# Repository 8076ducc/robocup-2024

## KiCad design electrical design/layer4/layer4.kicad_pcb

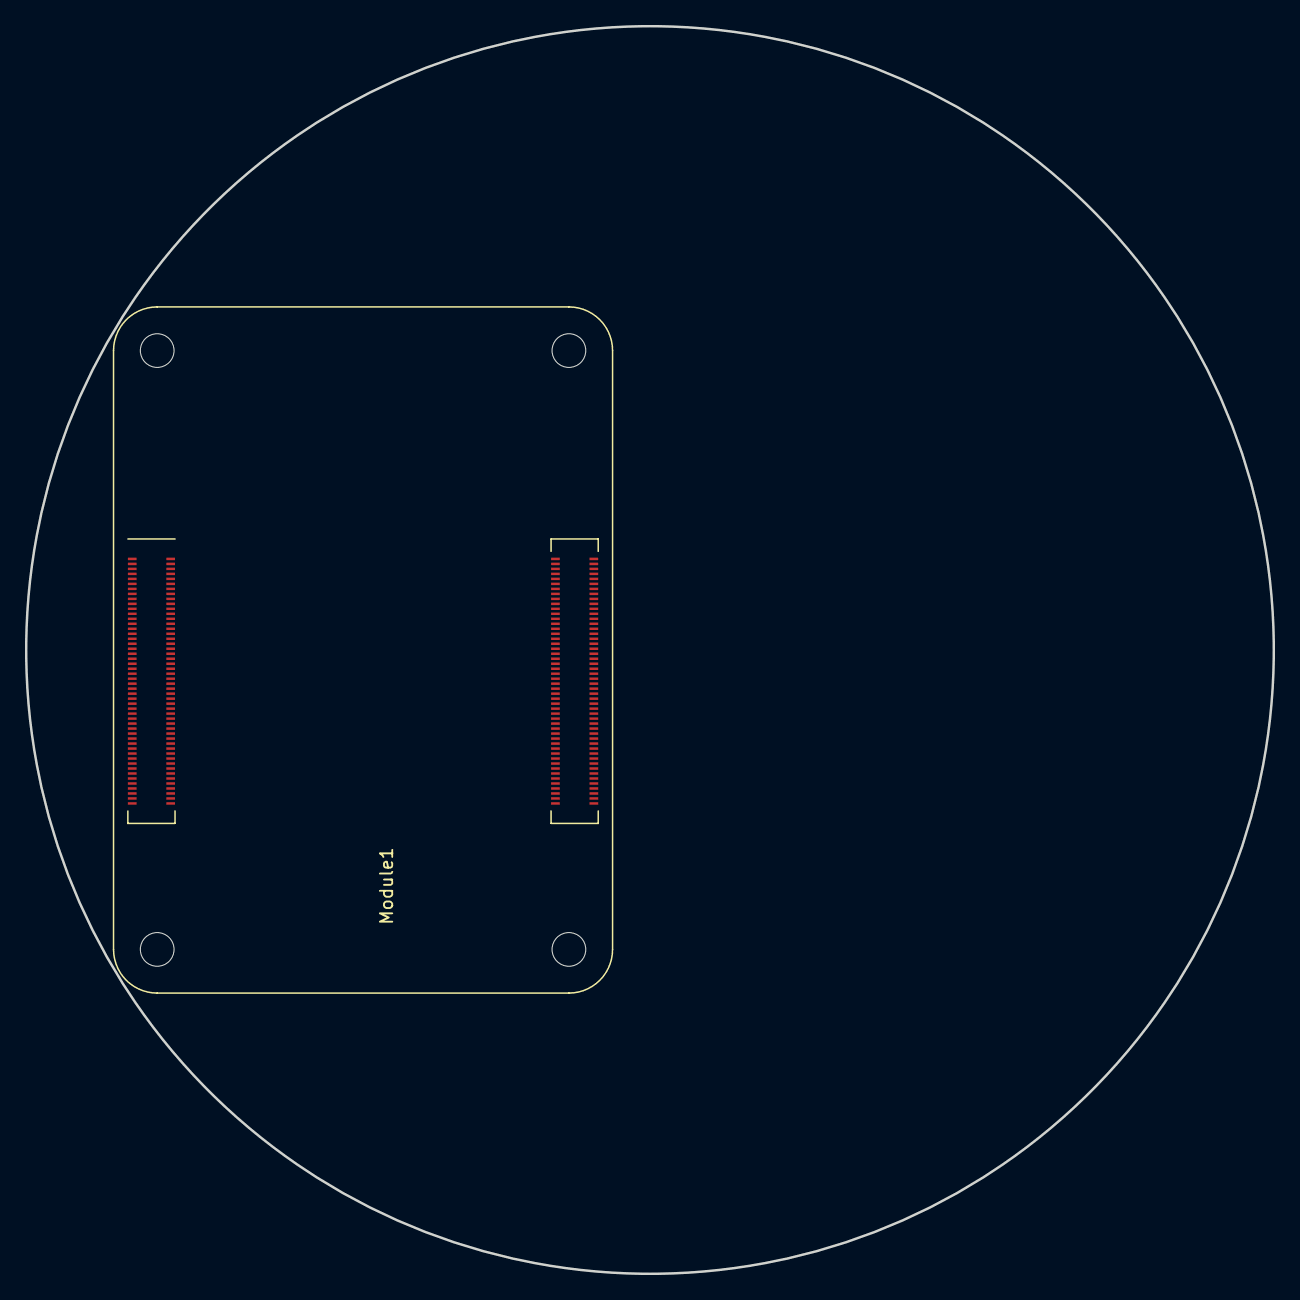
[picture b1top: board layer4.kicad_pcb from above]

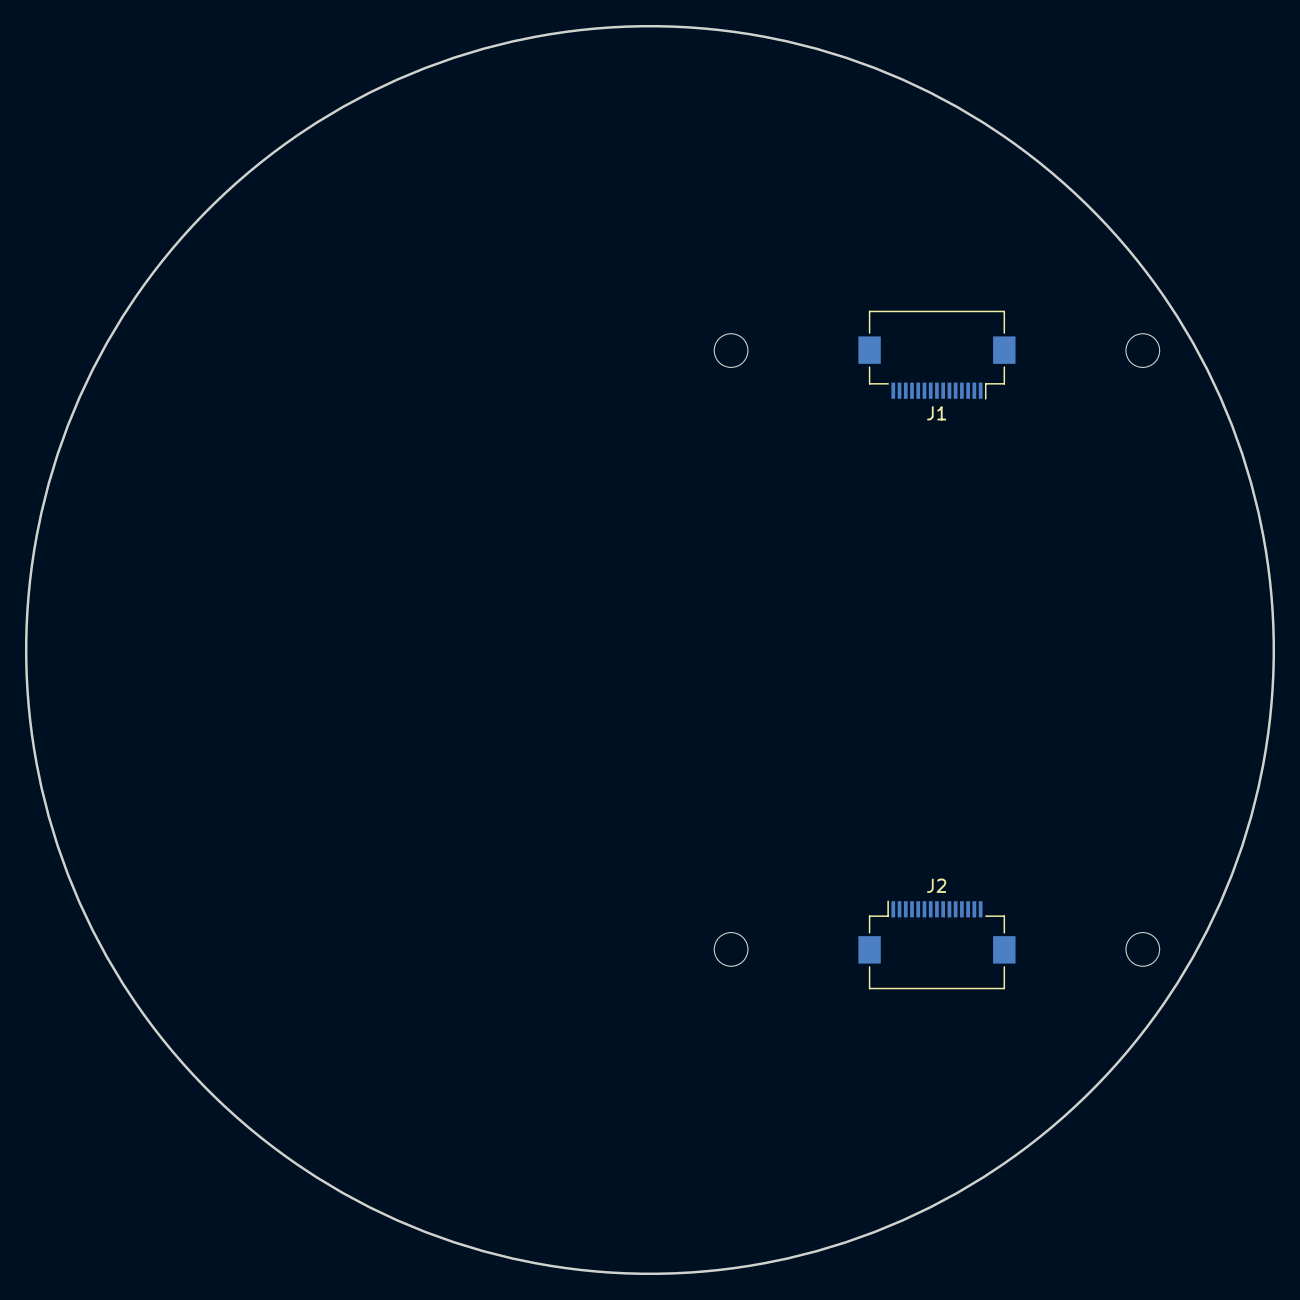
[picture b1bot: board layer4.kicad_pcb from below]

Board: 2 copper layers, 100.0 x 100.0 mm, 3 parts (2 on the bottom side), 20 nets, no tracks yet.

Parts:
J1, J2: Conn_01x15_Female; Hirose_FH12-15S-0.5SH_1x15-1MP_P0.50mm_Horizontal
Module1: ComputeModule4-CM4; Raspberry-Pi-4-Compute-Module

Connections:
+3V3: J1.15, J2.15, Module1.78 (GPIO_VREF(1.8v/3.3v_Input)), Module1.84 (+3.3v_(Output)), Module1.86 (+3.3v_(Output))
+5V: Module1.77 (+5v_(Input)), Module1.79 (+5v_(Input)), Module1.81 (+5v_(Input)), Module1.83 (+5v_(Input)), Module1.85 (+5v_(Input)), Module1.87 (+5v_(Input))
/rpi1/CAM0_C_N: J1.8, Module1.140 (CAM0_C_N)
/rpi1/CAM0_C_P: J1.9, Module1.142 (CAM0_C_P)
/rpi1/CAM0_D0_N: J1.2, Module1.128 (CAM0_D0_N)
/rpi1/CAM0_D0_P: J1.3, Module1.130 (CAM0_D0_P)
/rpi1/CAM0_D1_N: J1.5, Module1.134 (CAM0_D1_N)
/rpi1/CAM0_D1_P: J1.6, Module1.136 (CAM0_D1_P)
/rpi1/CAM1_C_N: J2.8, Module1.127 (CAM1_C_N)
/rpi1/CAM1_C_P: J2.9, Module1.129 (CAM1_C_P)
/rpi1/CAM1_D0_N: J2.2, Module1.115 (CAM1_D0_N)
/rpi1/CAM1_D0_P: J2.3, Module1.117 (CAM1_D0_P)
/rpi1/CAM1_D1_N: J2.5, Module1.121 (CAM1_D1_N)
/rpi1/CAM1_D1_P: J2.6, Module1.123 (CAM1_D1_P)
/rpi1/CAM_GPIO: J1.11, J2.11, Module1.97 (Camera_GPIO)
/rpi1/ID_SCL: J2.13, Module1.35 (ID_SC)
/rpi1/ID_SDA: J2.14, Module1.36 (ID_SD)
/rpi1/SCL0: J1.13, Module1.80 (SCL0)
/rpi1/SDA0: J1.14, Module1.82 (SDA0)
GND: J1.1, J1.4, J1.7, J1.10, J2.1, J2.4, J2.7, J2.10, Module1.1 (GND), Module1.2 (GND), Module1.7 (GND), Module1.8 (GND), Module1.13 (GND), Module1.14 (GND), Module1.22 (GND), Module1.23 (GND), Module1.32 (GND), Module1.33 (GND), Module1.42 (GND), Module1.43 (GND), Module1.52 (GND), Module1.53 (GND), Module1.59 (GND), Module1.60 (GND), Module1.65 (GND), Module1.66 (GND), Module1.71 (GND), Module1.74 (GND), Module1.98 (GND), Module1.107 (GND), Module1.108 (GND), Module1.113 (GND), Module1.114 (GND), Module1.119 (GND), Module1.120 (GND), Module1.125 (GND), Module1.126 (GND), Module1.131 (GND), Module1.132 (GND), Module1.137 (GND), Module1.138 (GND), Module1.144 (GND), Module1.150 (GND), Module1.155 (GND), Module1.156 (GND), Module1.161 (GND), Module1.162 (GND), Module1.167 (GND), Module1.168 (GND), Module1.173 (GND), Module1.174 (GND), Module1.179 (GND), Module1.180 (GND), Module1.185 (GND), Module1.186 (GND), Module1.191 (GND), Module1.192 (GND), Module1.197 (GND), Module1.198 (GND)

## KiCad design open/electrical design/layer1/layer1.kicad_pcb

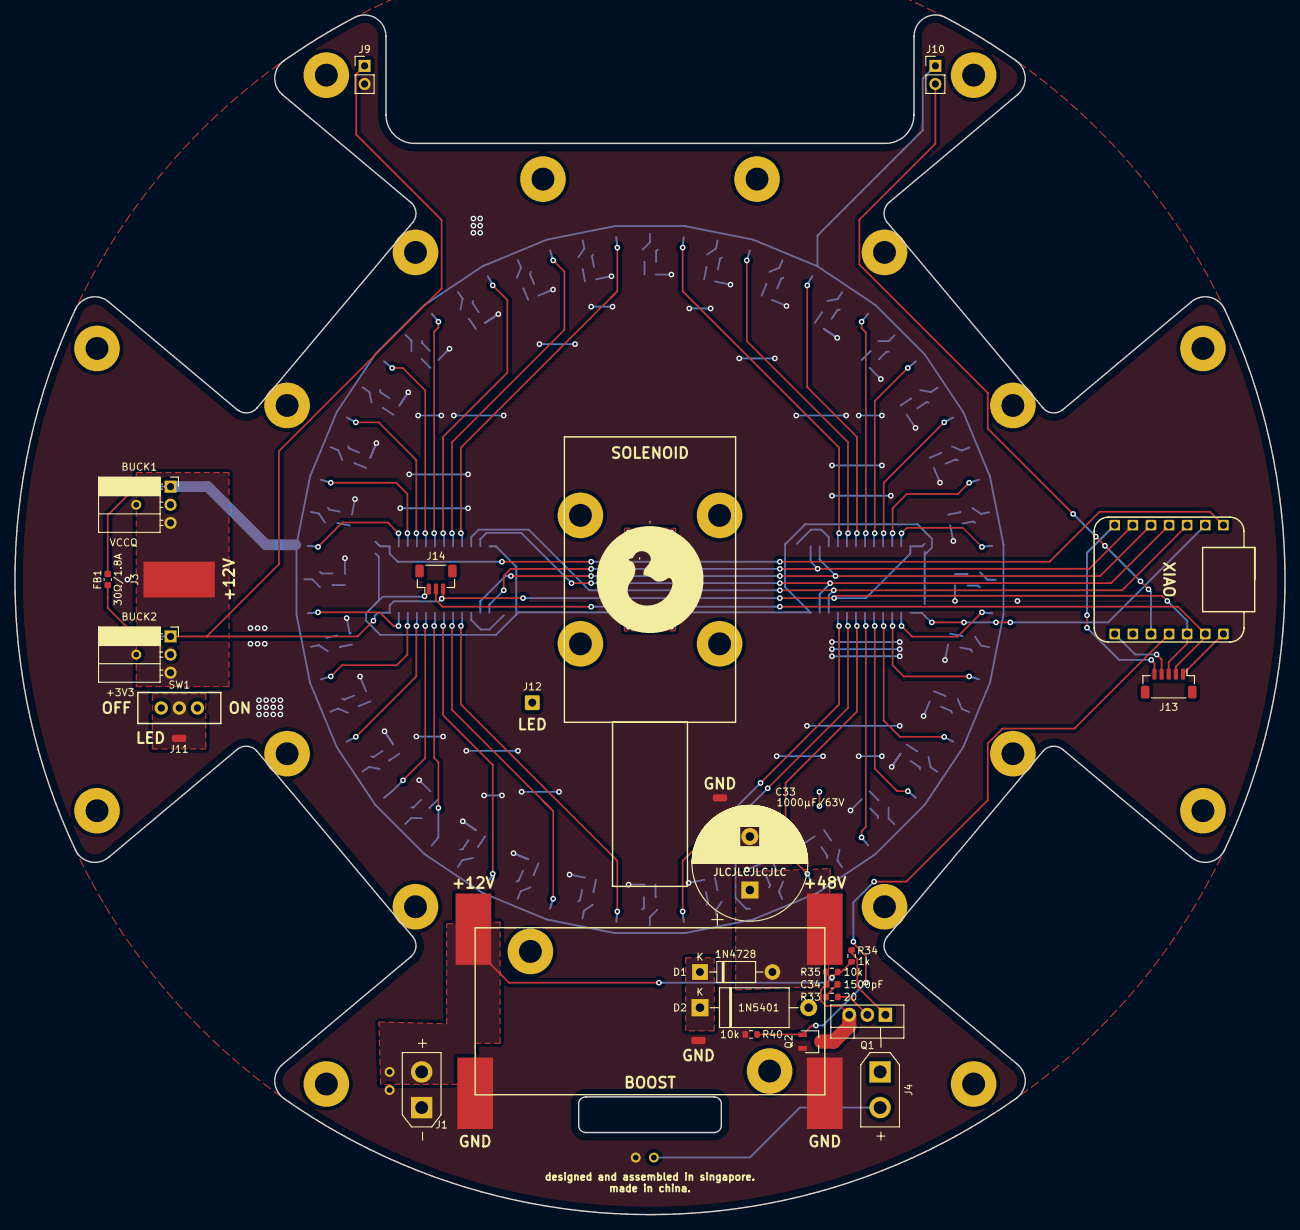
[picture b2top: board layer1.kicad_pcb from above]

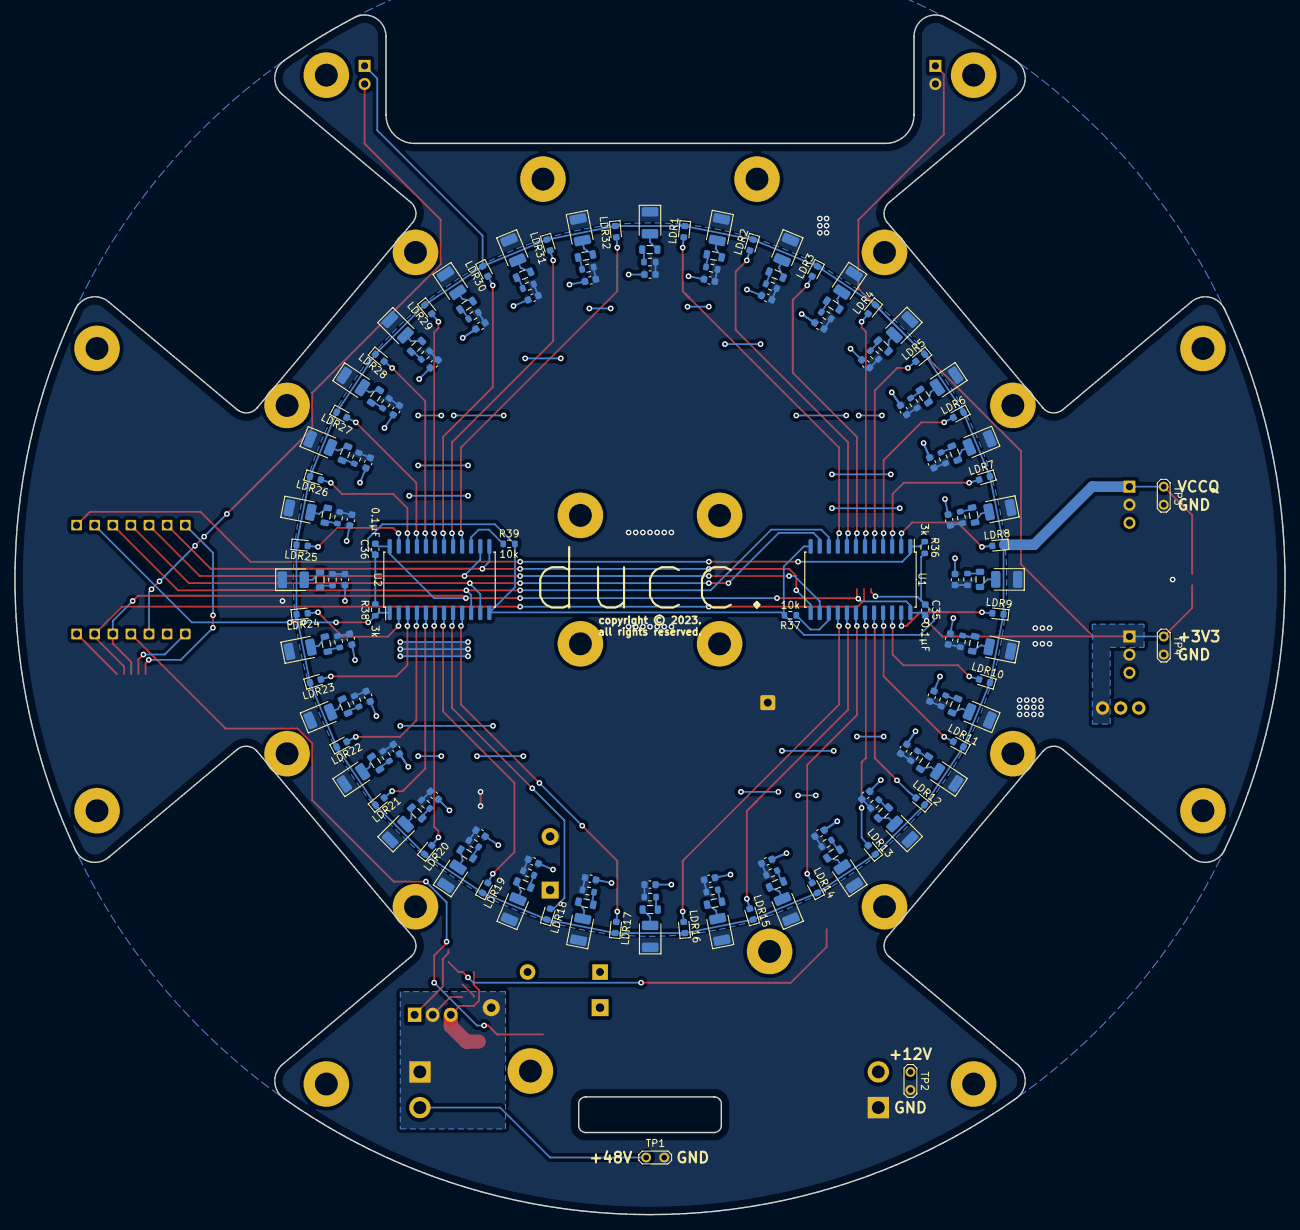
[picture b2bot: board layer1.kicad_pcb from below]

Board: 2 copper layers, 178.0 x 168.1 mm, 226 parts (172 on the bottom side), 122 nets.

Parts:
BUCK1: VCCQ; PinSocket_1x03_P2.54mm_Horizontal
BUCK2: +3V3; PinSocket_1x03_P2.54mm_Horizontal
C1, C2, C3, C4, C5, C6, C7, C8, C9, C10, C11, C12, C13, C14, C15, C16, C17, C18, C19, C20, C21, C22, C23, C24, C25, C26, C27, C28, C29, C30, C31, C32: 1uF; C_0603_1608Metric
C33: 1000µF/63V; CP_Radial_D16.0mm_P7.50mm
C34: 1500pF; C_0603_1608Metric
C35, C36: 0.1μF; C_0603_1608Metric
D1: 1N4728; D_DO-41_SOD81_P10.16mm_Horizontal
D2: 1N5401; D_DO-27_P15.24mm_Horizontal
FB1: 30Ω/1.8A; C_0603_1608Metric
H1, H2, H3, H4, H5, H6, H7, H8, H9, H10, H11, H12, H13, H14, H15, H16, H17, H18, H19, H20, H21, H22, H23, H24: MountingHole; MountingHole_3.2mm_M3_Pad
J1: XT30-F; AMASS_XT30UPB-F_1x02_P5.0mm_Vertical
J2, J11, J15: Conn_01x01_Socket; SolderWirePad_1x01_SMD_1x2mm
J3, J5, J6, J7, J8: Conn_01x01_Socket; SolderWirePad_1x01_SMD_5x10mm
J4: XT30PW-F; AMASS_XT30UPB-F_1x02_P5.0mm_Vertical
J9, J10: Conn_01x02_Pin; PinHeader_1x02_P2.54mm_Vertical
J12: Conn_01x01_Socket; SolderWire-0.5sqmm_1x01_D0.9mm_OD2.1mm
J13: SH1.0 5P; JST_SH_BM05B-SRSS-TB_1x05-1MP_P1.00mm_Vertical
J14: SH1.0 3P; JST_SH_BM03B-SRSS-TB_1x03-1MP_P1.00mm_Vertical
L1, L2, L3, L4, L5, L6, L7, L8, L9, L10, L11, L12, L13, L14, L15, L16, L17, L18, L19, L20, L21, L22, L23, L24, L25, L26, L27, L28, L29, L30, L31, L32: 10µH; L_0805_2012Metric
LDR1, LDR2, LDR3, LDR4, LDR5, LDR6, LDR7, LDR8, LDR9, LDR10, LDR11, LDR12, LDR13, LDR14, LDR15, LDR16, LDR17, LDR18, LDR19, LDR20, LDR21, LDR22, LDR23, LDR24, LDR25, LDR26, LDR27, LDR28, LDR29, LDR30, LDR31, LDR32: ALS-PT19-315C; D_0603_1608Metric
LED1, LED2, LED3, LED4, LED5, LED6, LED7, LED8, LED9, LED10, LED11, LED12, LED13, LED14, LED15, LED16, LED17, LED18, LED19, LED20, LED21, LED22, LED23, LED24, LED25, LED26, LED27, LED28, LED29, LED30, LED31, LED32: WHITE 3528; CP_EIA-3528-12_Kemet-T
Q1: MOSFET-NCH-FQP30N06L; TO-220-3_Vertical
Q2: MOSFET-NCH-AO3404A; TSOT-23
R1, R2, R3, R4, R5, R6, R7, R8, R9, R10, R11, R12, R13, R14, R15, R16, R17, R18, R19, R20, R21, R22, R23, R24, R25, R26, R27, R28, R29, R30, R31, R32: 0R39; R_0603_1608Metric
R33: 20; R_0603_1608Metric
R34: 1k; R_0603_1608Metric
R35, R37, R39, R40: 10k; R_0603_1608Metric
R36, R38: 3k; R_0603_1608Metric
SW1: SW_SPDT; SWITCH_SPDT_PTH_11.6X4.0MM
TP1, TP2, TP3, TP4: TestPoint_2Pole; TestPoint_2Pads_Pitch2.54mm_Drill0.8mm
U1, U2: CD74HC4067SM; SOIC-24W_7.5x15.4mm_P1.27mm
U3: MOUDLE-SEEEDUINO-XIAO-ESP32C3; xiao-esp32c3

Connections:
+3V3: BUCK2.1, C35.1, C36.1, FB1.1, J9.1, J13.3, J14.3, SW1.1 (A), TP4.1, U1.24 (VCC), U2.24 (VCC), U3.12 (3V3)
+5V: J13.1, U3.14 (5V)
+12V: BUCK1.3, BUCK2.3, J1.2, J3.1, J5.1, R34.1, R35.1, TP2.1
+48V: C33.1, D1.2 (A), J4.2, J7.1, TP1.1
/BALL: J10.2, U3.10 (PA5_A9_D9_MISO)
/LED: C1.1, C2.1, C3.1, C4.1, C5.1, C6.1, C7.1, C8.1, C9.1, C10.1, C11.1, C12.1, C13.1, C14.1, C15.1, C16.1, C17.1, C18.1, C19.1, C20.1, C21.1, C22.1, C23.1, C24.1, C25.1, C26.1, C27.1, C28.1, C29.1, C30.1, C31.1, C32.1, J11.1, J12.1, R1.1, R2.1, R3.1, R4.1, R5.1, R6.1, R7.1, R8.1, R9.1, R10.1, R11.1, R12.1, R13.1, R14.1, R15.1, R16.1, R17.1, R18.1, R19.1, R20.1, R21.1, R22.1, R23.1, R24.1, R25.1, R26.1, R27.1, R28.1, R29.1, R30.1, R31.1, R32.1, SW1.2 (B)
/MUX1OUT: R36.1, U1.1 (COM), U3.1 (PA02_A0_D0)
/MUX2OUT: R38.1, U2.1 (COM), U3.2 (PA4_A1_D1)
/RX: J13.4, U3.8 (PB09_A7_D7_RX)
/S0: U1.10 (S0), U2.10 (S0), U3.3 (PA10_A2_D2)
/S1: U1.11 (S1), U2.11 (S1), U3.4 (PA11_A3_D3)
/S2: U1.14 (S2), U2.14 (S2), U3.5 (PA8_A4_D4_SDA)
/S3: U1.13 (S3), U2.13 (S3), U3.6 (PA9_A5_D5_SCL)
/SOLENOIDON: Q2.1 (G), R40.1, U3.11 (PA6_A10_D10_MOSI)
/TX: J13.5, U3.7 (PB08_A6_D6_TX)
GND: BUCK1.2, BUCK2.2, C1.2, C2.2, C3.2, C4.2, C5.2, C6.2, C7.2, C8.2, C9.2, C10.2, C11.2, C12.2, C13.2, C14.2, C15.2, C16.2, C17.2, C18.2, C19.2, C20.2, C21.2, C22.2, C23.2, C24.2, C25.2, C26.2, C27.2, C28.2, C29.2, C30.2, C31.2, C32.2, C33.2, J1.1, J2.1, J6.1, J8.1, J9.2, J15.1, LED1.1 (K), LED2.1 (K), LED3.1 (K), LED4.1 (K), LED5.1 (K), LED6.1 (K), LED7.1 (K), LED8.1 (K), LED9.1 (K), LED10.1 (K), LED11.1 (K), LED12.1 (K), LED13.1 (K), LED14.1 (K), LED15.1 (K), LED16.1 (K), LED17.1 (K), LED18.1 (K), LED19.1 (K), LED20.1 (K), LED21.1 (K), LED22.1 (K), LED23.1 (K), LED24.1 (K), LED25.1 (K), LED26.1 (K), LED27.1 (K), LED28.1 (K), LED29.1 (K), LED30.1 (K), LED31.1 (K), LED32.1 (K), Q2.2 (S), R40.2, TP1.2, TP2.2, TP3.2, TP4.2
GNDA: C35.2, C36.2, J14.1, R36.2, R37.2, R38.2, R39.2, U1.12 (GND), U2.12 (GND)
GNDD: J13.2, J14.2, U3.13 (GND)
unnamed: C34.1, R33.2
unnamed: D1.1 (K), D2.1 (K)
unnamed: D2.2 (A), J4.1, Q1.2 (D), R33.1
unnamed: L1.2, R1.2
unnamed: L2.2, R2.2
unnamed: L3.2, R3.2
unnamed: L4.2, R4.2
unnamed: L5.2, R5.2
unnamed: L6.2, R6.2
unnamed: L7.2, R7.2
unnamed: L8.2, R8.2
unnamed: L9.2, R9.2
unnamed: L10.2, R10.2
unnamed: L11.2, R11.2
unnamed: L12.2, R12.2
unnamed: L13.2, R13.2
unnamed: L14.2, R14.2
unnamed: L15.2, R15.2
unnamed: L16.2, R16.2
unnamed: L17.2, R17.2
unnamed: L18.2, R18.2
unnamed: L19.2, R19.2
unnamed: L20.2, R20.2
unnamed: L21.2, R21.2
unnamed: L22.2, R22.2
unnamed: L23.2, R23.2
unnamed: L24.2, R24.2
unnamed: L25.2, R25.2
unnamed: L26.2, R26.2
unnamed: L27.2, R27.2
unnamed: L28.2, R28.2
unnamed: L29.2, R29.2
unnamed: L30.2, R30.2
unnamed: L31.2, R31.2
unnamed: L32.2, R32.2
unnamed: L1.1, LED1.2 (A)
unnamed: L2.1, LED2.2 (A)
unnamed: L3.1, LED3.2 (A)
unnamed: L4.1, LED4.2 (A)
unnamed: L5.1, LED5.2 (A)
unnamed: L6.1, LED6.2 (A)
unnamed: L7.1, LED7.2 (A)
unnamed: L8.1, LED8.2 (A)
unnamed: L9.1, LED9.2 (A)
unnamed: L10.1, LED10.2 (A)
unnamed: L11.1, LED11.2 (A)
unnamed: L12.1, LED12.2 (A)
unnamed: L13.1, LED13.2 (A)
unnamed: L14.1, LED14.2 (A)
unnamed: L15.1, LED15.2 (A)
unnamed: L16.1, LED16.2 (A)
unnamed: L17.1, LED17.2 (A)
unnamed: L18.1, LED18.2 (A)
unnamed: L19.1, LED19.2 (A)
unnamed: L20.1, LED20.2 (A)
unnamed: L21.1, LED21.2 (A)
unnamed: L22.1, LED22.2 (A)
unnamed: L23.1, LED23.2 (A)
unnamed: L24.1, LED24.2 (A)
unnamed: L25.1, LED25.2 (A)
unnamed: L26.1, LED26.2 (A)
unnamed: L27.1, LED27.2 (A)
unnamed: L28.1, LED28.2 (A)
unnamed: L29.1, LED29.2 (A)
unnamed: L30.1, LED30.2 (A)
unnamed: L31.1, LED31.2 (A)
unnamed: L32.1, LED32.2 (A)
unnamed: Q1.1 (G), R34.2
unnamed: C34.2, Q1.3 (S), Q2.3 (D), R35.2
unnamed: LDR1.2, U1.9 (I0)
unnamed: LDR2.2, U1.8 (I1)
unnamed: LDR3.2, U1.7 (I2)
unnamed: LDR4.2, U1.6 (I3)
unnamed: LDR5.2, U1.5 (I4)
unnamed: LDR6.2, U1.4 (I5)
unnamed: LDR7.2, U1.3 (I6)
unnamed: LDR8.2, U1.2 (I7)
unnamed: LDR9.2, U1.23 (I8)
unnamed: LDR10.2, U1.22 (I9)
unnamed: LDR11.2, U1.21 (I10)
unnamed: LDR12.2, U1.20 (I11)
unnamed: LDR13.2, U1.19 (I12)
unnamed: LDR14.2, U1.18 (I13)
unnamed: LDR15.2, U1.17 (I14)
unnamed: LDR16.2, U1.16 (I15)
unnamed: R37.1, U1.15 (~E)
unnamed: LDR17.2, U2.9 (I0)
unnamed: LDR18.2, U2.8 (I1)
unnamed: LDR19.2, U2.7 (I2)
unnamed: LDR20.2, U2.6 (I3)
unnamed: LDR21.2, U2.5 (I4)
unnamed: LDR22.2, U2.4 (I5)
unnamed: LDR23.2, U2.3 (I6)
unnamed: LDR24.2, U2.2 (I7)
unnamed: LDR25.2, U2.23 (I8)
unnamed: LDR26.2, U2.22 (I9)
unnamed: LDR27.2, U2.21 (I10)
unnamed: LDR28.2, U2.20 (I11)
unnamed: LDR29.2, U2.19 (I12)
unnamed: LDR30.2, U2.18 (I13)
unnamed: LDR31.2, U2.17 (I14)
unnamed: LDR32.2, U2.16 (I15)
unnamed: R39.1, U2.15 (~E)
VCCQ: BUCK1.1, FB1.2, J10.1, LDR1.1, LDR2.1, LDR3.1, LDR4.1, LDR5.1, LDR6.1, LDR7.1, LDR8.1, LDR9.1, LDR10.1, LDR11.1, LDR12.1, LDR13.1, LDR14.1, LDR15.1, LDR16.1, LDR17.1, LDR18.1, LDR19.1, LDR20.1, LDR21.1, LDR22.1, LDR23.1, LDR24.1, LDR25.1, LDR26.1, LDR27.1, LDR28.1, LDR29.1, LDR30.1, LDR31.1, LDR32.1, TP3.1

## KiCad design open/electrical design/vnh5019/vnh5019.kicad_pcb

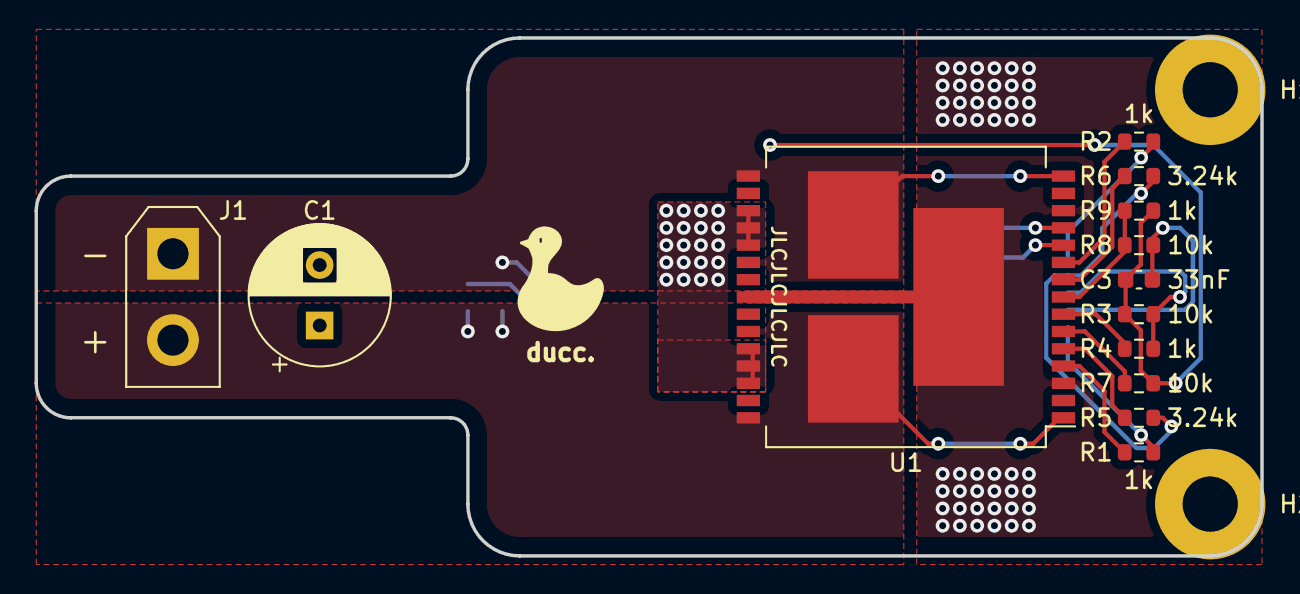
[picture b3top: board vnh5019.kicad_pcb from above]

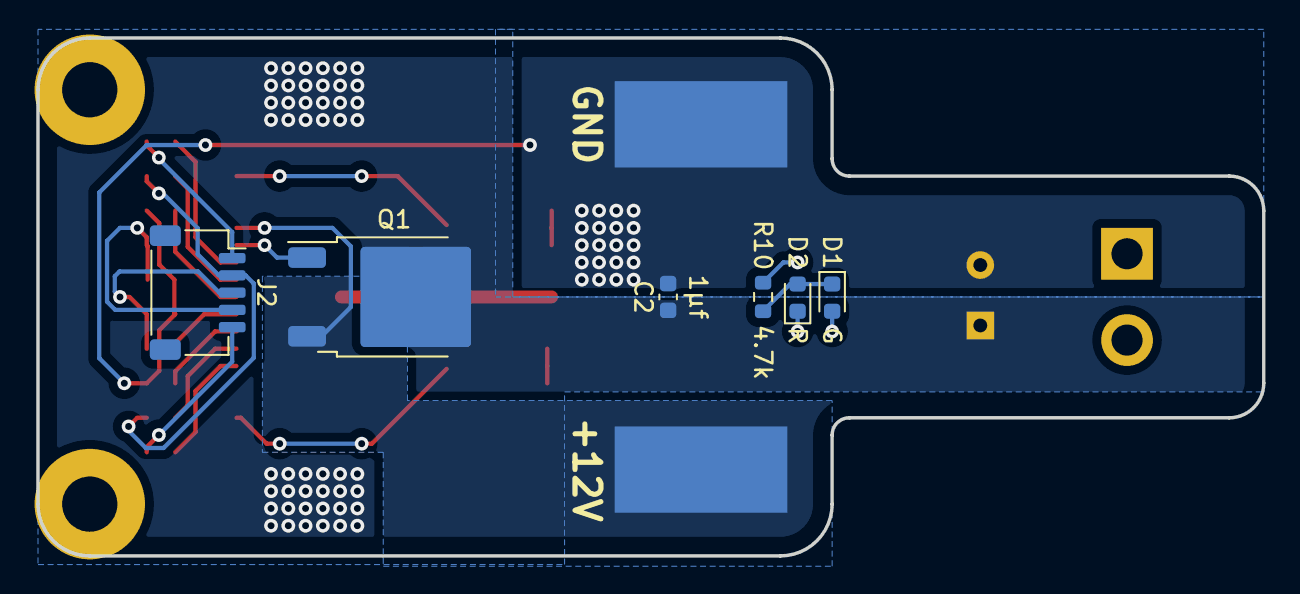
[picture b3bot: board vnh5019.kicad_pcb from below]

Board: 2 copper layers, 71.0 x 30.0 mm, 23 parts (8 on the bottom side), 19 nets.

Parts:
C1: 680µF; CP_Radial_D8.0mm_P3.50mm
C2: 1µf; C_0603_1608Metric
C3: 33nF; C_0603_1608Metric
D1: G; D_0603_1608Metric
D2: R; D_0603_1608Metric
H1, H2: MountingHole; MountingHole_3.2mm_M3_Pad
J1: XT30UPBF; AMASS_XT30UPB-F_1x02_P5.0mm_Vertical
J2: SH1.0 5P; JST_SH_SM05B-SRSS-TB_1x05-1MP_P1.00mm_Horizontal
J3, J4: Conn_01x01_Female; SolderWirePad_1x01_SMD_5x10mm
Q1: Q_NMOS_GDS; TO-252-2
R1, R2, R4, R9: 1k; R_0603_1608Metric
R3, R7, R8: 10k; R_0603_1608Metric
R5, R6: 3.24k; R_0603_1608Metric
R10: 4.7k; R_0603_1608Metric
U1: VNH5019A-E; ST_MultiPowerSO-30

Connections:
+12V: J3.1, Q1.3 (S), U1.12 (VBAT)
/CP: Q1.1 (G), U1.11 (CP)
/CS: C3.1, J2.4, R8.1
/EN: J2.2, R5.1, R6.1
/INA: J2.5, R1.1
/INB: J2.1, R2.1
/OUTA: D1.2 (A), D2.1 (K), J1.2, U1.1 (OUTA), U1.25 (OUTA), U1.30 (OUTA), U1.33 (OUTA)
/OUTB: J1.1, R10.2, U1.15 (OUTB), U1.16 (OUTB), U1.21 (OUTB), U1.32 (OUTB)
/PWM: J2.3, R3.2, R4.1
GND: C1.2, C2.2, C3.2, J4.1, R3.1, R7.1, R9.1, U1.18 (GNDB), U1.19 (GNDB), U1.20 (GNDB), U1.26 (GNDA), U1.27 (GNDA), U1.28 (GNDA)
unnamed: D1.1 (K), D2.2 (A), R10.1
unnamed: C1.1, C2.1, Q1.2 (D), U1.3 (VCC), U1.13 (VCC), U1.23 (VCC), U1.31 (VCC)
unnamed: R8.2, R9.2, U1.8 (CS)
unnamed: R7.2, U1.6 (CS_DIS)
unnamed: R5.2, U1.5 (EN/DIAGA)
unnamed: R6.2, U1.9 (EN/DIAGB)
unnamed: R1.2, U1.4 (INA)
unnamed: R2.2, U1.10 (INB)
unnamed: R4.2, U1.7 (PWM)

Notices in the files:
open/electrical design/layer1/layer1.kicad_pcb:
copyright © 2023.
all rights reserved.
